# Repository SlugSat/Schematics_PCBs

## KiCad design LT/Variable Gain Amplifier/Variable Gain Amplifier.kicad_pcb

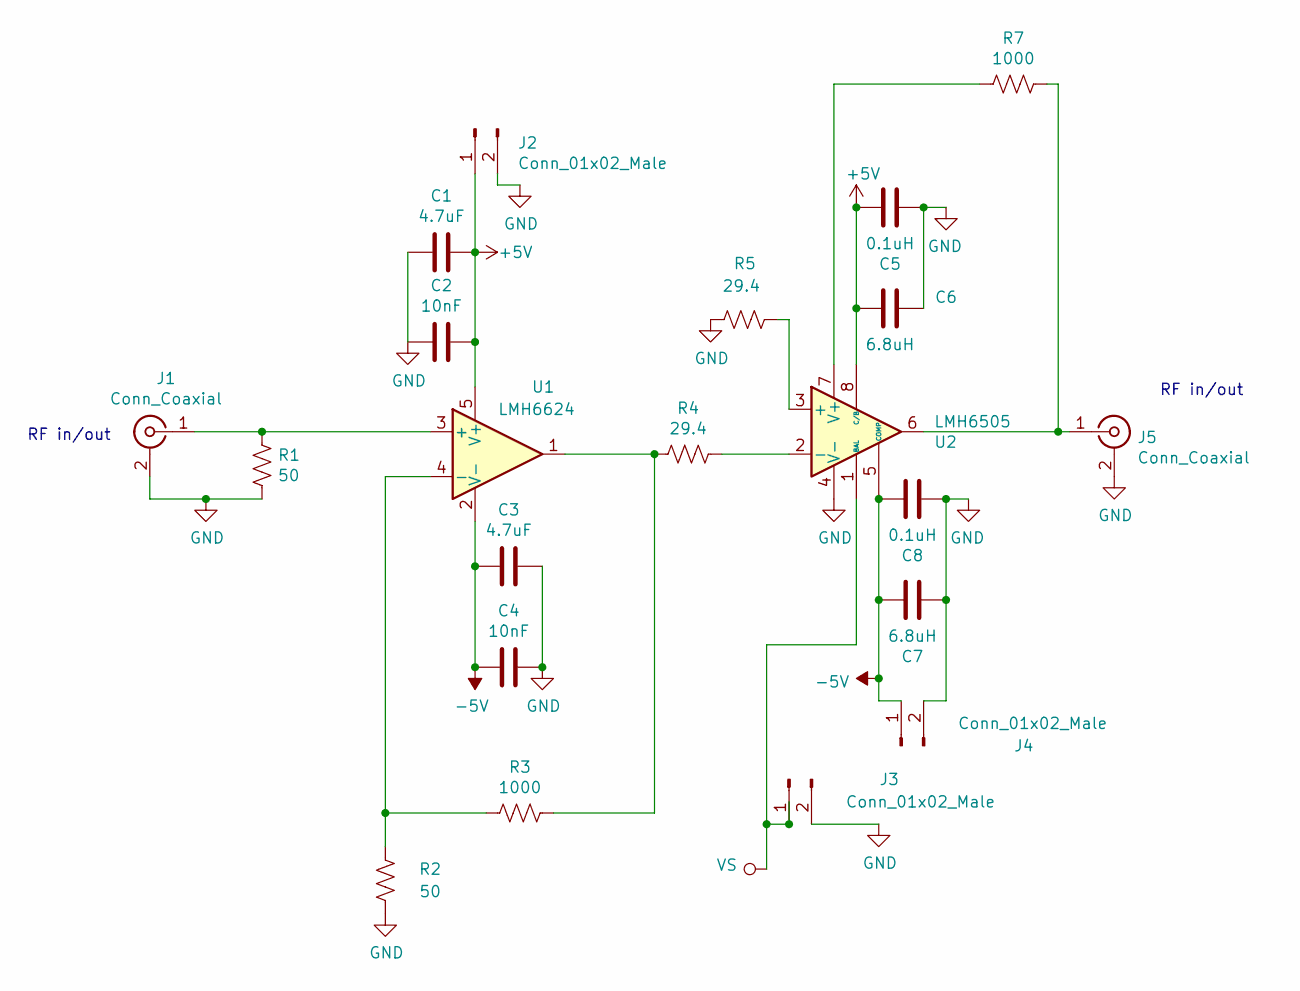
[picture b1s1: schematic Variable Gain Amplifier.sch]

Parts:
C1, C3: 4.7uF; C_0805_2012Metric_Pad1.15x1.40mm_HandSolder
C2, C4: 10nF; C_0805_2012Metric_Pad1.15x1.40mm_HandSolder
C5, C8: 0.1uH; C_0805_2012Metric_Pad1.15x1.40mm_HandSolder
C6, C7: 6.8uH; C_0805_2012Metric_Pad1.15x1.40mm_HandSolder
J1, J5: Conn_Coaxial; SMA_Amphenol_132289_EdgeMount
J2, J3, J4: Conn_01x02_Male; PinHeader_1x02_P2.54mm_Vertical
R1, R2: 50; R_0805_2012Metric_Pad1.15x1.40mm_HandSolder
R3, R7: 1000; R_0805_2012Metric_Pad1.15x1.40mm_HandSolder
R4, R5: 29.4; R_0805_2012Metric_Pad1.15x1.40mm_HandSolder
U1: LMH6624; SOT-23-5
U2: LMH6505; SOIC-8_3.9x4.9mm_P1.27mm

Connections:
+5V: C1.1, C2.1, C5.2, C6.2, J2.1, U1.5 (V+), U2.8 (C/B)
-5V: C3.2, C4.2, C7.2, C8.2, J4.1, U1.2 (V-), U2.5 (COMP)
GND: C1.2, C2.2, C3.1, C4.1, C5.1, C6.1, C7.1, C8.1, J1.2 (Ext), J2.2, J3.2, J4.2, J5.2 (Ext), R1.1, R2.2, R5.2, U2.4 (V-)
unnamed: J1.1 (In), R1.2, U1.3 (+)
unnamed: J5.1 (In), R7.1, U2.6
unnamed: R2.1, R3.2, U1.4 (-)
unnamed: R3.1, R4.2, U1.1
unnamed: R4.1, U2.2 (-)
unnamed: R5.1, U2.3 (+)
unnamed: R7.2, U2.7 (V+)
VS: J3.1, U2.1 (BAL)

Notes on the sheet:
RF in/out

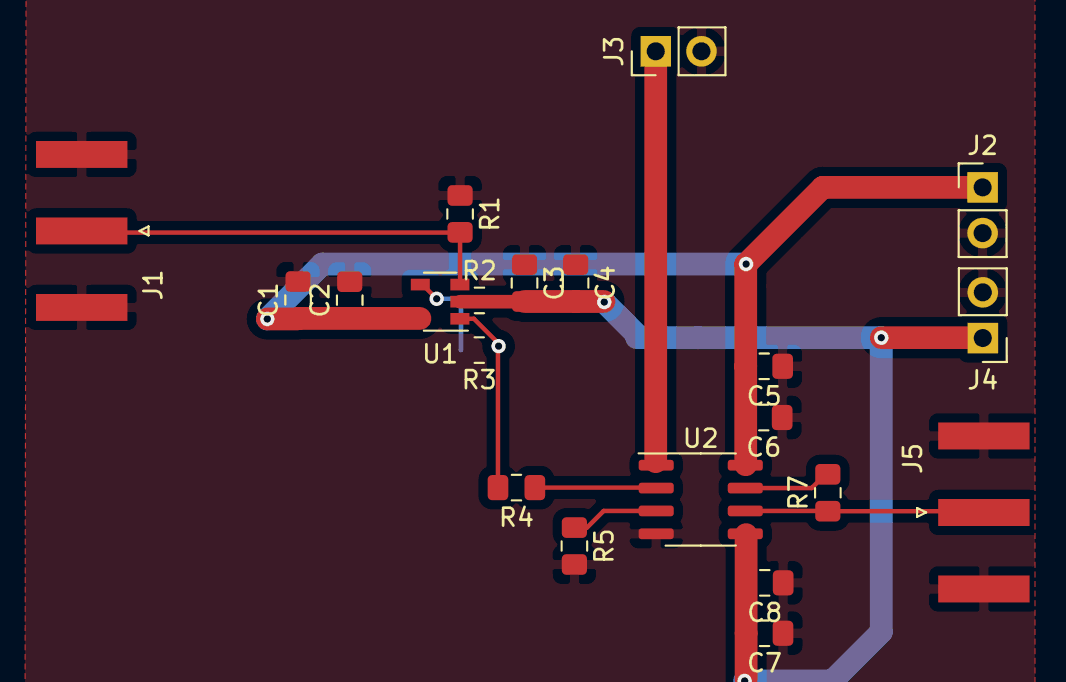
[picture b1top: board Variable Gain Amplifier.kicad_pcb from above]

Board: 2 copper layers, 21 parts (0 on the bottom side), 11 nets.

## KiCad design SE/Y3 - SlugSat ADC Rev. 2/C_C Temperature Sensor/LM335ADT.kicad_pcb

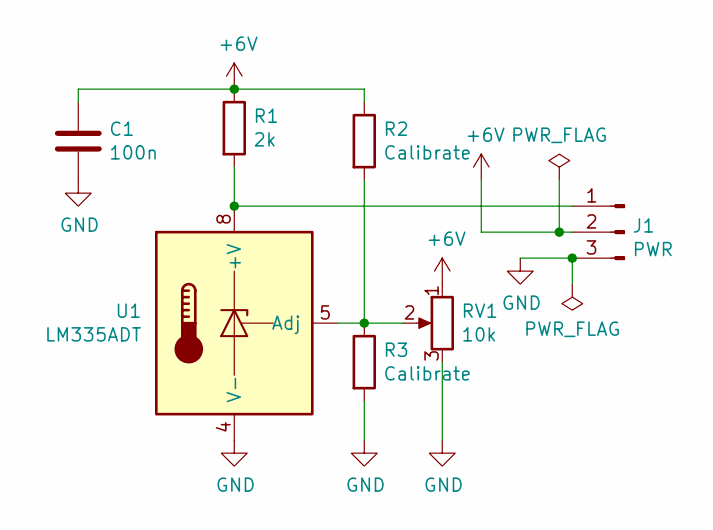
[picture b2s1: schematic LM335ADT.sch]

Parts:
C1: 100n; C_0805_2012Metric_Pad1.15x1.40mm_HandSolder
J1: PWR; PinHeader_1x03_P2.54mm_Vertical
R1: 2k; R_0805_2012Metric_Pad1.15x1.40mm_HandSolder
R2, R3: Calibrate; R_0805_2012Metric_Pad1.15x1.40mm_HandSolder
RV1: 10k; Potentiometer_Bourns_3266Y_Vertical
U1: LM335ADT; SO-8_3.9x4.9mm_P1.27mm

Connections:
+6V: C1.1, J1.2, R1.1, R2.1, RV1.1
GND: C1.2, J1.3, R3.2, RV1.3, U1.4 (V-)
unnamed: J1.1, R1.2, U1.8 (+V)
unnamed: R2.2, R3.1, RV1.2, U1.5 (Adj)

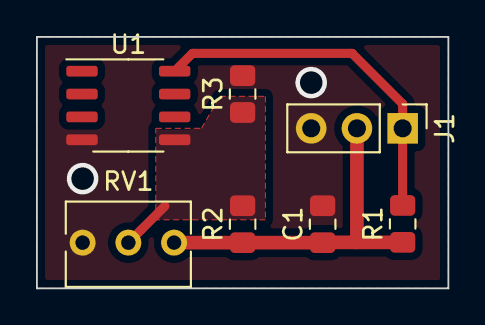
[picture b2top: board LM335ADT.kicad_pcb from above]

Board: 2 copper layers, 22.9 x 14.0 mm, 7 parts (0 on the bottom side), 4 nets.

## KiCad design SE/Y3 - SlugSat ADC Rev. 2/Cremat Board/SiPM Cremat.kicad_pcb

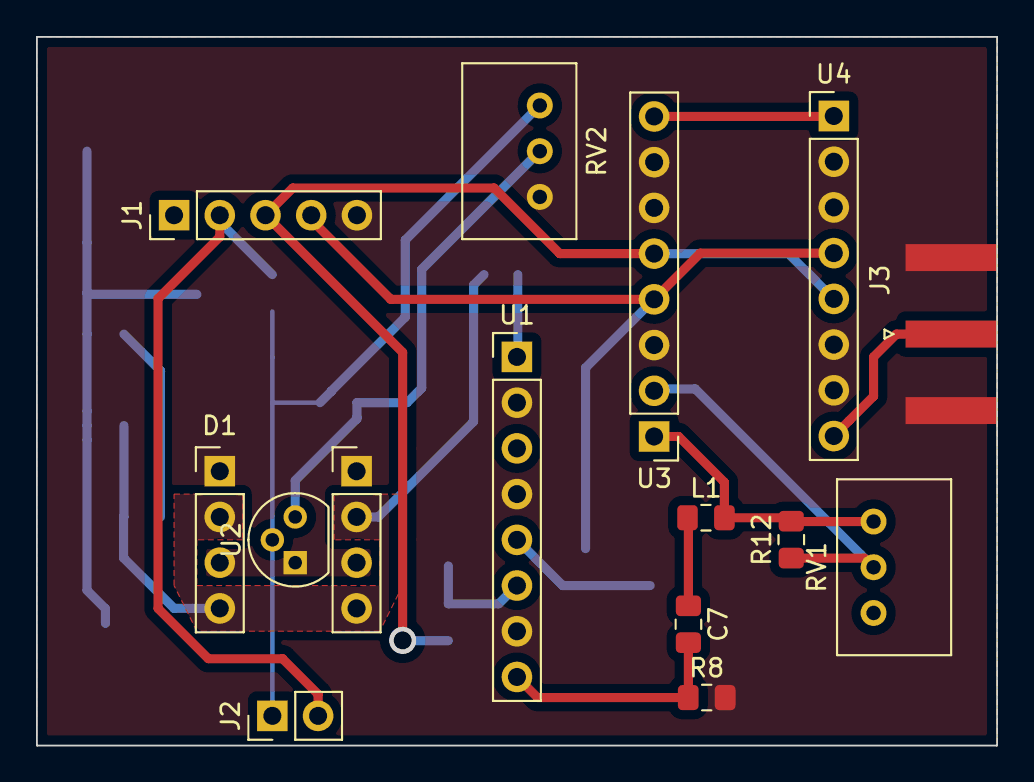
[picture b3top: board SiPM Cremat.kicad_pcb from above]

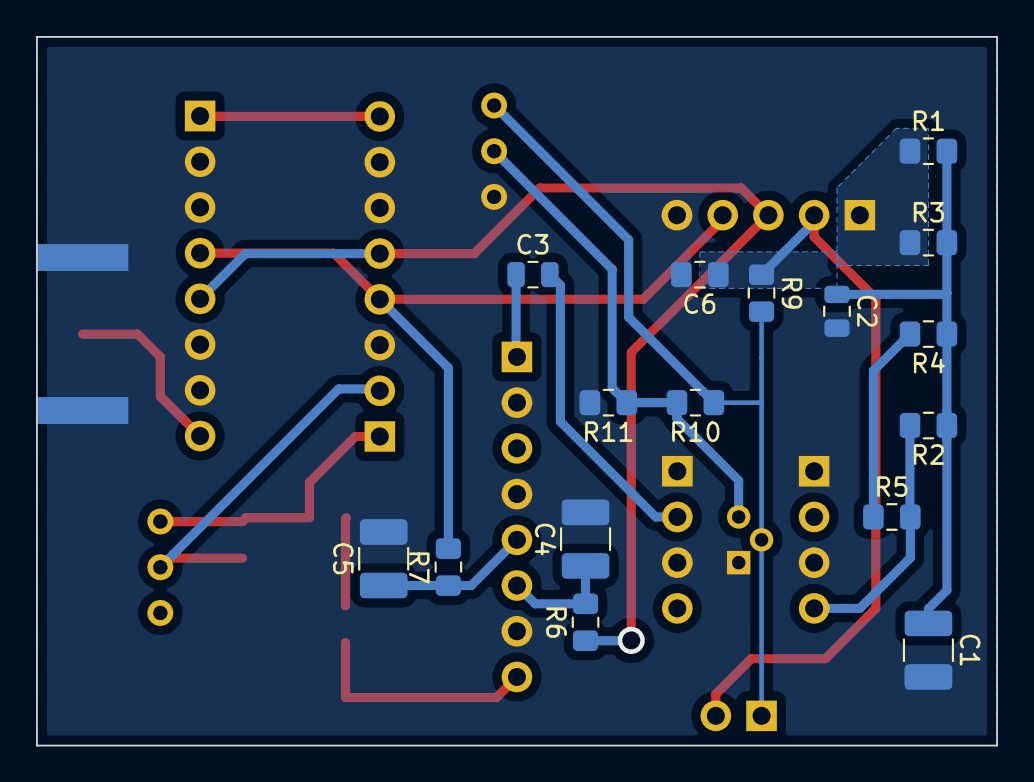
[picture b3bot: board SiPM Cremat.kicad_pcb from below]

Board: 2 copper layers, 53.3 x 39.4 mm, 30 parts (16 on the bottom side), 19 nets.

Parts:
C1, C4, C5: 10u; C_1210_3225Metric_Pad1.42x2.65mm_HandSolder
C2, C3: 0.01u; C_0805_2012Metric
C6: 100n; C_0805_2012Metric_Pad1.15x1.40mm_HandSolder
C7: 1u; C_0805_2012Metric_Pad1.15x1.40mm_HandSolder
D1: ArrayJ-60035-4P-PCB
J1: PWR; PinHeader_1x05_P2.54mm_Vertical
J2: Temp. Out; PinHeader_1x02_P2.54mm_Vertical
J3: Conn_Coaxial; SMA_Amphenol_132289_EdgeMount
L1: 10u; L_0805_2012Metric_Pad1.15x1.40mm_HandSolder
R1, R3: 10M; R_0805_2012Metric_Pad1.15x1.40mm_HandSolder
R2, R4, R5: 100M; R_0805_2012Metric_Pad1.15x1.40mm_HandSolder
R6, R7: 47; R_0805_2012Metric_Pad1.15x1.40mm_HandSolder
R8: 1k; R_0805_2012Metric_Pad1.15x1.40mm_HandSolder
R9: 2k; R_0805_2012Metric_Pad1.15x1.40mm_HandSolder
R10, R11: Cal.; R_0805_2012Metric_Pad1.15x1.40mm_HandSolder
R12: P/Z Trim; R_0805_2012Metric_Pad1.15x1.40mm_HandSolder
RV1, RV2: R_POT; Potentiometer_Bourns_3299W_Vertical
U1: CR-113-R2.1; PinHeader_1x08_P2.54mm_Vertical
U2: LM335AZ_NOPB; TO-92
U3: CR-200-R2.1; PinHeader_1x08_P2.54mm_Vertical
U4: CR-210-R0; PinHeader_1x08_P2.54mm_Vertical

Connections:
+3V3: C6.1, J1.2, J2.2, R9.1
+6V: J1.3, R6.1, U3.5, U4.5
+36V: J1.1, R1.1, R3.1
-6V: J1.4, R7.2, U3.4, U4.4
GND: C1.2, C2.2, C4.2, C5.2, C6.2, D1.1, D1.3, D1.6, D1.8, J1.5, J3.2, R8.2, R11.2, RV2.1, U1.2, U1.4, U1.7, U2.1, U3.3, U3.6, U3.7, U4.2, U4.3, U4.6, U4.7
unnamed: C1.1, C2.1, R1.2, R2.1, R3.2, R4.1
unnamed: C3.1, U1.1
unnamed: C3.2, D1.2, D1.4, D1.5, D1.7, R2.2, R5.2
unnamed: C4.1, R6.2, U1.6
unnamed: C5.1, R7.1, U1.5
unnamed: C7.1, L1.1
unnamed: C7.2, R8.1, U1.8
unnamed: J2.1, R9.2, R10.1, RV2.3, U2.2
unnamed: J3.1, U4.8
unnamed: L1.2, R12.2, RV1.1, U3.1
unnamed: R4.2, R5.1
unnamed: R10.2, R11.1, RV2.2, U2.3
unnamed: R12.1, RV1.2, U3.2
unnamed: U3.8, U4.1
